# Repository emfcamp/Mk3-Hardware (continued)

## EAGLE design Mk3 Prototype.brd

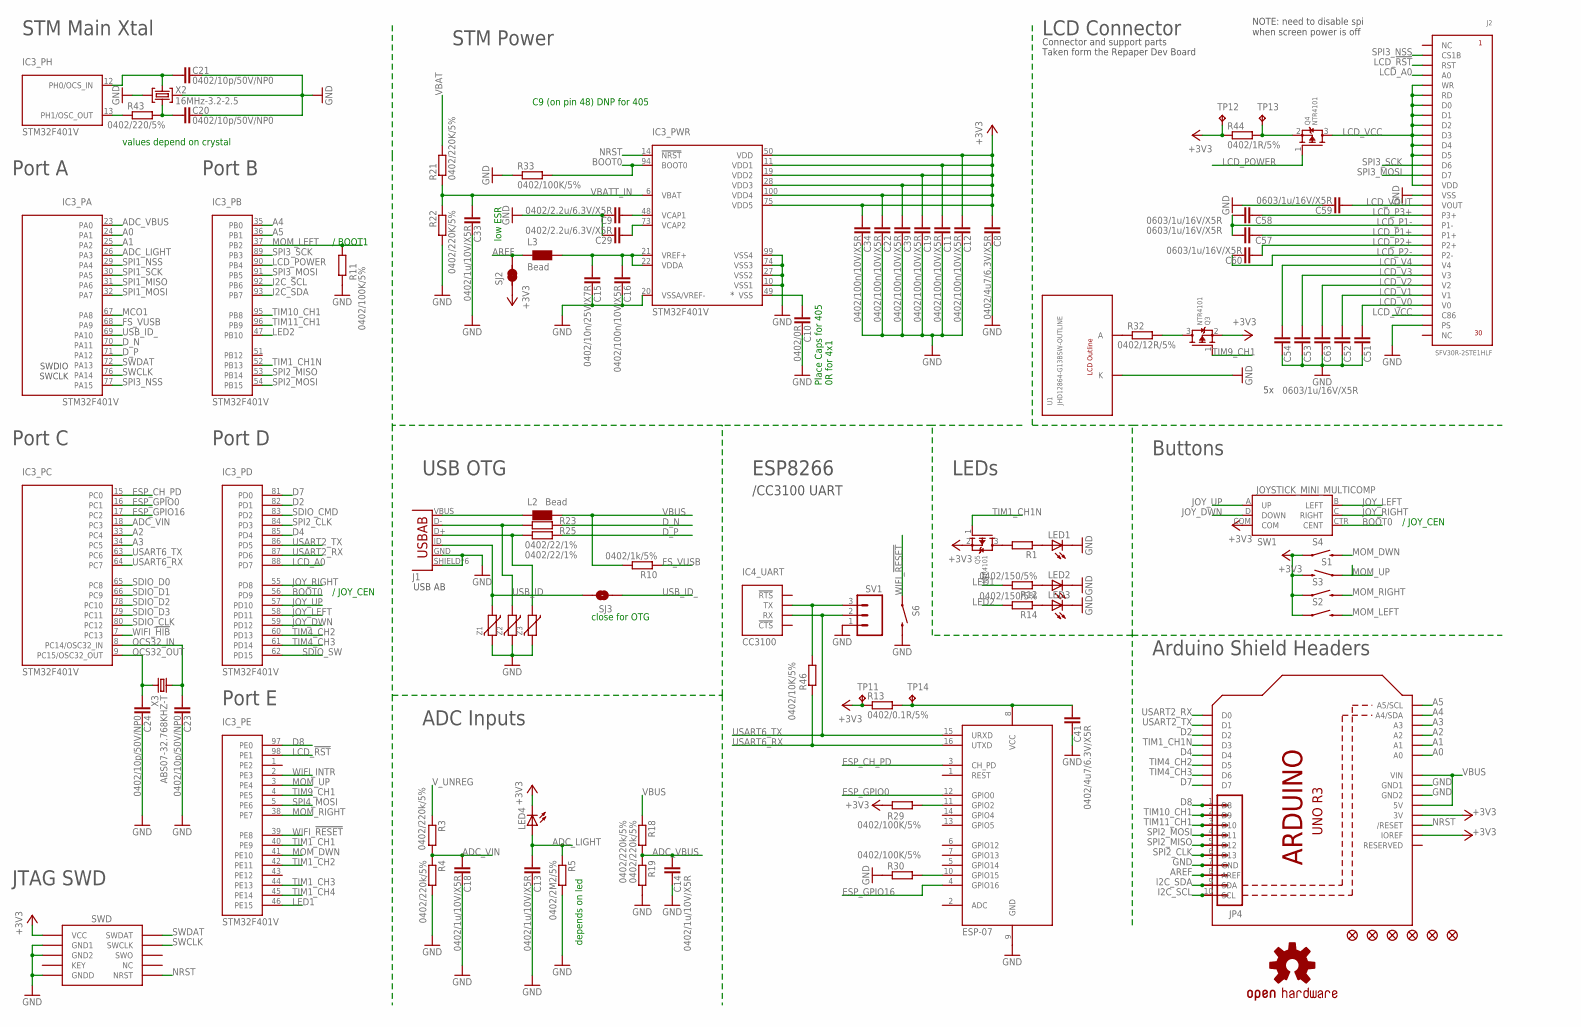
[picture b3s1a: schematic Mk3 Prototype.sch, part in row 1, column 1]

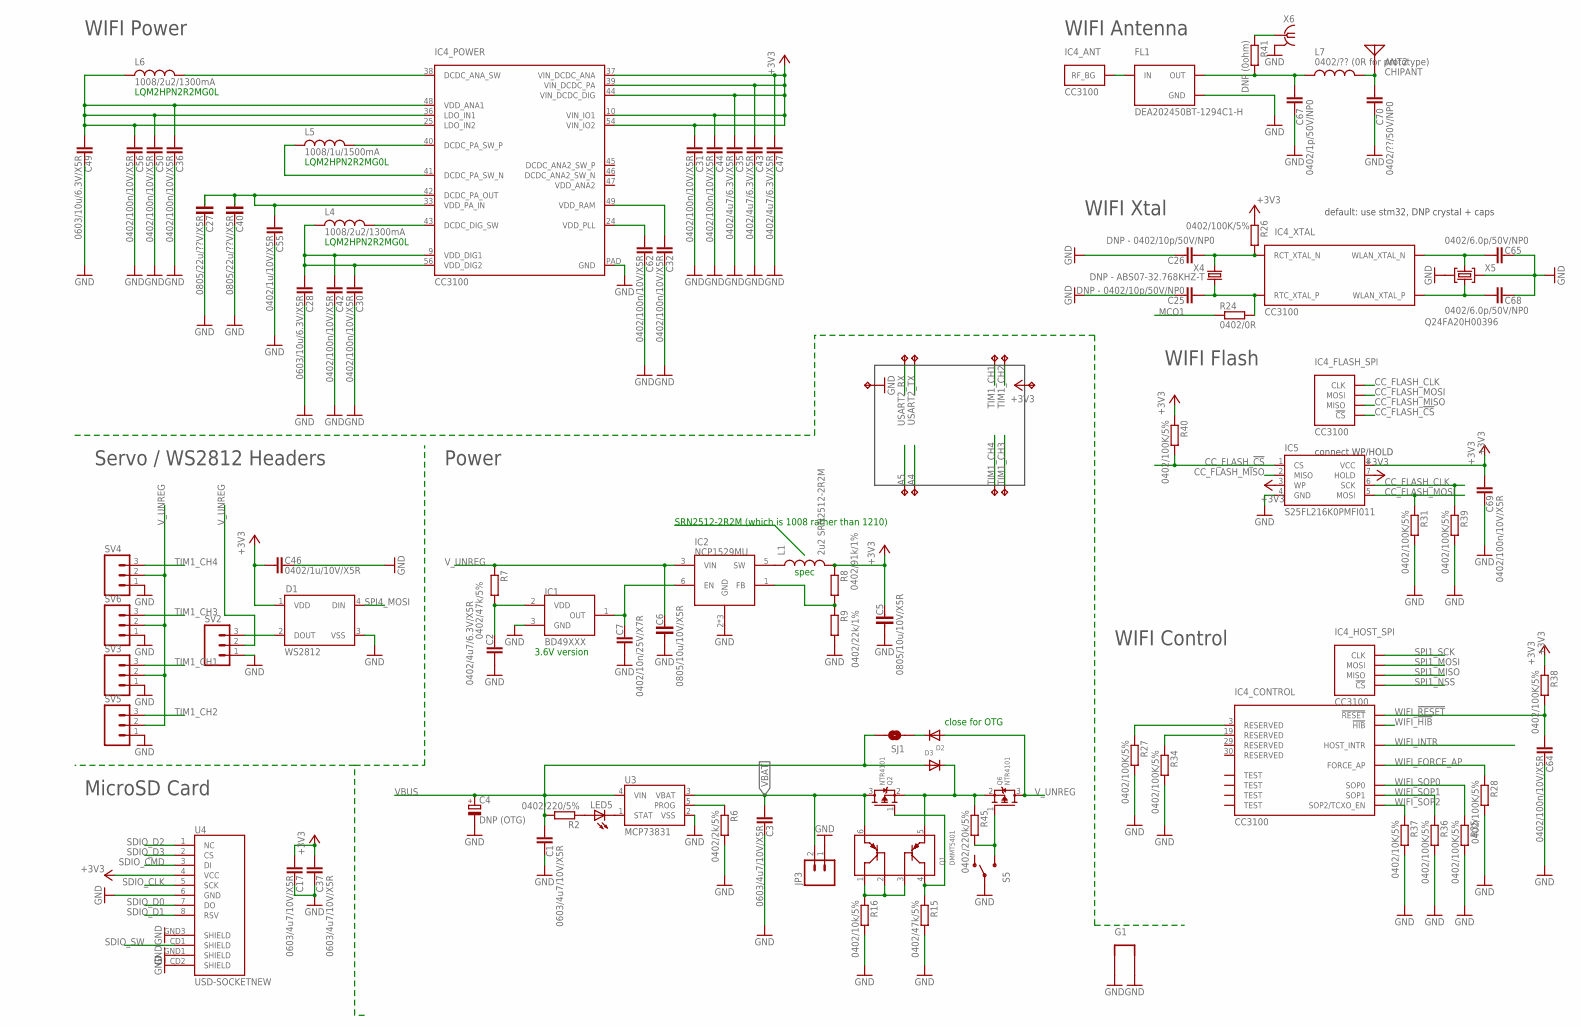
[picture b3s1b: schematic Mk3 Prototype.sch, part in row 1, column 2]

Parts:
ANT2: CHIPANT; 2450AT42A100
C1: 0603/4u7/10V/X5R; C0805K
C2, C8, C35, C41, C43, C47: 0402/4u7/6.3V/X5R; C0402-SMALLER
C3, C17, C37: 0603/4u7/10V/X5R; C0603K-SMALL
C4: DNP (OTG); E2,5-6
C5, C6: 0805/10u/10V/X5R; C0805-N
C7, C15: 0402/10n/25V/X7R; C0402-SMALLER
C9, C29: 0402/2.2u/6.3V/X5R; C0402-SMALLER
C10: 0402/0R; C0402-SMALLER
C11, C12, C16, C19, C22, C30, C31, C32, C34, C36, C39, C42, C44, C50, C56, C62, C64, C69: 0402/100n/10V/X5R; C0402-SMALLER
C13, C14, C18, C33, C46, C55: 0402/1u/10V/X5R; C0402-SMALLER
C20, C21, C23, C24: 0402/10p/50V/NP0; C0402-SMALLER
C25, C26: DNP - 0402/10p/50V/NP0; C0402-SMALLER
C27, C40: 0805/22u/??V/X5R; C0805-N
C28, C49: 0603/10u/6.3V/X5R; C0603K-SMALL
C51, C52, C53, C54, C57, C58, C59, C60, C63: 0603/1u/16V/X5R; C0603K-SMALL
C65, C68: 0402/6.0p/50V/NP0; C0402-SMALLER
C67: 0402/1p/50V/NP0; C0402-SMALLER
C70: 0402/??/50V/NP0; C0402-SMALLER
D1: WS2812B
D2, D3: DIODESOD-323F; SOD-323F
FID1, FID2, FID3, FID4, FID5, FID6: FIDUCIAL1X2.5-STOP; FIDUCIAL-1X2.5-STOP
FL1: DEA202450BT-1294C1-H; DEA202450BT
G1: GND-LOOP
IC1: BD49XXX; SSOP5
IC2: NCP1529MU; DFN6
IC3: STM32F401V; TQFP100
IC4: CC3100; VQFN-64
IC5: S25FL216K0PMFI011; SO08-EIAJ
J1: ZX62-AB-5PA(11); USB-AB-MICRO-SMD_LWK
J2: SFV30R-2STE1HLF
J3: SWD_SHROUD; SWD_PTH_SHROUD
JP3: M02-JST-2MM-SMT; JST-2-SMD
JP4: M10NOSILK; 1X10-NOSILK
L1: 2u2 SRN2512-2R2M; 1210
L2, L3: Bead; WUERTH-0805
L4, L6: 1008/2u2/1300mA; 1008
L5: 1008/1u/1500mA; 1008
L7: 0402/?? (0R for prototype); L0402
LED1: LED5MM
LED2, LED3, LED4, LED5: LED0603-CORRECT; LED-0603-CORRECT
LOGO1: OSHW-LOGOM; OSHW-LOGO-M
Q1: DMMT5401; SOT26
Q2, Q3, Q4, Q5, Q6: NTR4101; SOT23-R
R1: R-EU_0207/10; 0207/10
R2, R43: 0402/220/5%; R0402-SMALLER
R3, R4, R18, R19, R45: 0402/220k/5%; R0402-SMALLER
R5: 0402/2M2/5%; R0402-SMALLER
R6: 0402/2k/5%; R0402-SMALLER
R7, R15: 0402/47k/5%; R0402-SMALLER
R8: 0402/91k/1%; R0402-SMALLER
R9: 0402/22k/1%; R0402-SMALLER
R10: 0402/1k/5%; R0402-SMALLER
R11, R26, R27, R28, R29, R30, R31, R33, R34, R35, R36, R38, R39, R40: 0402/100K/5%; R0402-SMALLER
R12, R14: 0402/150/5%; R0402-SMALLER
R13: 0402/0.1R/5%; R0402-SMALLER
R16: 0402/10k/5%; R0402-SMALLER
R21, R22: 0402/220K/5%; R0402-SMALLER
R23, R25: 0402/22/1%; R0402-SMALLER
R24: 0402/0R; R0402-SMALLER
R32: 0402/12R/5%; R0402-SMALLER
R37, R46: 0402/10K/5%; R0402-SMALLER
R41: DNP (0ohm); R0402-SMALLER
R44: 0402/1R/5%; R0402-SMALLER
S1, S2, S3, S4: SWITCH-MOMENTARY-2; TACTILE_SWITCH_TALL
S5: SWITCH-SPST-SMD-A
S6: SWITCH-MOMENTARY-2SMD-1101NE; TACTILE-SWITCH-1101NE
SJ1, SJ3: JUMPER-PAD-2-NOYES_SILK; PAD-JUMPER-2-NO_YES_SILK
SJ2: SOLDERJUMPERTRACE; SJ_2S-TRACE
SV1, SV2, SV3, SV4, SV5, SV6: M03PTH; 1X03
SW1: JOYSTICK_MINI_MULTICOMP; JOYSTICK_MULTICOMP
TP1, TP2, TP3, TP4, TP5, TP6, TP7, TP8, TP9, TP10: TP4MM; 4MMEDGE
TP11, TP12, TP13, TP14: TPB1,27; B1,27
U1: JHD12864-G13BSW-OUTLINE
U2: ARDUINOR3-NODIM
U3: MCP73831; SOT23-5
U4: USD-SOCKETNEW; MICRO-SD-SOCKET-PP
X1: ESP-07
X2: 16MHz-3.2-2.5; CRYSTAL-3.2-2.5
X3: ABS07-32.768KHZ-T; RESONATOR_EPSON_FC_145
X4: DNP - ABS07-32.768KHZ-T; RESONATOR_EPSON_FC_145
X5: Q24FA20H00396; CRYSTAL-2.5X2.0
X6: MC-921
Z1, Z2, Z3: VARISTORCN0603; CT/CN0603

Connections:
+3V3: C5.1, C8.2, C11.2, C12.2, C17.2, C19.2, C22.2, C31.2, C34.2, C35.2, C37.2, C39.2, C43.2, C44.2, C46.2, C47.2, C69.2, D1.1 (VDD), IC3.11 (VDD1), IC3.19 (VDD2), IC3.28 (VDD3), IC3.50 (VDD), IC3.75 (VDD5), IC3.100 (VDD4), IC4.10 (VIN_IO1), IC4.37 (VIN_DCDC_ANA), IC4.39 (VIN_DCDC_PA), IC4.44 (VIN_DCDC_DIG), IC4.54 (VIN_IO2), IC5.3 (WP), IC5.7 (HOLD), IC5.8 (VCC), J3.1 (VCC), L1.2, LED4.C, Q3.2 (S), Q5.2 (S), R8.1, R13.1, R26.1, R29.1, R38.1, R40.1, R44.1, S1.B2 (2), S2.A2 (1), S3.A2 (1), S4.A2 (1), SJ2.1, SW1.COM, TP6.P$1, TP11.TP, TP12.TP, U2.3V, U2.IOREF, U4.4 (VCC)
A0: IC3.24 (PA1), U2.A0
A1: IC3.25 (PA2), U2.A1
A2: IC3.33 (PC4), U2.A2
A3: IC3.34 (PC5), U2.A3
A4: IC3.35 (PB0), TP8.P$1, U2.A4 (A4/SDA)
A5: IC3.36 (PB1), TP7.P$1, U2.A5 (A5/SCL)
ADC_LIGHT: C13.2, IC3.26 (PA3), LED4.A, R5.1
ADC_VBUS: C14.2, IC3.23 (PA0), R18.2, R19.1
ADC_VIN: C18.2, IC3.18 (PC3), R3.2, R4.1
ANT: ANT2.P$1, C70.1, L7.2
AREF: JP4.8, L3.1, SJ2.2, U2.AREF
BOOT0: IC3.56 (PD9), IC3.94 (BOOT0), R33.2, SW1.CTR (CENT)
CC_FLASH_!CS: IC4.14 (!CS), IC5.1 (CS), R40.2
CC_FLASH_CLK: IC4.11 (CLK), IC5.6 (SCK), R39.1
CC_FLASH_MISO: IC4.13 (MISO), IC5.2 (MISO)
CC_FLASH_MOSI: IC4.12 (MOSI), IC5.5 (MOSI), R31.1
CHARGING: LED5.C, U3.1 (STAT)
D2: IC3.82 (PD1), U2.D2
D4: IC3.85 (PD4), U2.D4
D7: IC3.81 (PD0), U2.D7
D8: IC3.97 (PE0), JP4.1, U2.D8
DFGFDG: C15.2, C16.2, IC3.21 (VREF+), IC3.22 (VDDA), L3.2
D_N: IC3.70 (PA11), R23.1
D_P: IC3.71 (PA12), R25.1
ESP_CH_PD: IC3.15 (PC0), X1.3 (CH_PD)
ESP_GPIO0: IC3.16 (PC1), X1.12 (GPIO0)
ESP_GPIO16: IC3.17 (PC2), X1.4 (GPIO16)
FS_VUSB: IC3.68 (PA9), R10.1
GND: C1.1, C2.2, C3.1, C4.-, C5.2, C6.2, C7.2, C8.1, C9.1, C10.1, C11.1, C12.1, C13.1, C14.1, C15.1, C16.1, C17.1, C18.1, C19.1, C20.1, C21.1, C22.1, C23.1, C24.1, C25.1, C26.1, C27.1, C28.1, C29.1, C30.1, C31.1, C32.1, C33.1, C34.1, C35.1, C36.1, C37.1, C39.1, C40.1, C41.1, C42.1, C43.1, C44.1, C46.1, C47.1, C49.1, C50.1, C51.1, C52.1, C53.1, C54.1, C55.1, C56.1, C59.1, C62.1, C63.1, C64.1, C65.1, C67.2, C68.1, C69.1, C70.2, D1.3 (VSS), FL1.GND@2 (GND), FL1.GND@4 (GND), G1.P$3 (1), G1.P$4 (2), IC1.3 (GND), IC2.2 (GND), IC2.4 (GND), IC2.EP (GND), IC3.10 (VSS1), IC3.20 (VSSA/VREF-), IC3.27 (VSS2), IC3.74 (VSS3), IC3.99 (VSS4), IC4.PAD (GND), IC5.4 (GND), J1.GND, J1.SHIELD, J1.SHIELD@0 (SHIELD), J1.SHIELD@1 (SHIELD), J1.SHIELD@2 (SHIELD), J1.SHIELD@3 (SHIELD), J1.SHIELD@5 (SHIELD), J2.16 (VSS), J2.29 (PS), J2.M1 (VSS), J2.M2 (VSS), J3.3 (GND1), J3.5 (GND2), J3.9 (GNDD), JP3.1, JP4.7, LED1.K (C), LED2.C, LED3.C, R4.2, R5.2, R6.2, R9.2, R11.1, R15.2, R16.2, R19.2, R22.2, R27.2, R28.2, R30.1, R31.2, R33.1, R34.2, R35.2, R36.2, R37.2, R39.2, S5.2, S6.2, SV1.1, SV2.1, SV3.1, SV4.1, SV5.1, SV6.1, TP5.P$1, U1.K, U2.GND, U2.GND1, U2.GND2, U3.2 (VSS), U4.6 (GND), U4.CD2 (SHIELD), U4.GND1 (SHIELD), U4.GND3 (SHIELD), X1.9 (GND), X2.2 (GND), X2.4 (GND)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
I2C_SCL: IC3.92 (PB6), JP4.10, U2.SCL
I2C_SDA: IC3.93 (PB7), JP4.9, U2.SDA
JOY_DWN: IC3.59 (PD12), SW1.D (DOWN)
JOY_LEFT: IC3.58 (PD11), SW1.B (LEFT)
JOY_RIGHT: IC3.55 (PD8), SW1.C (RIGHT)
JOY_UP: IC3.57 (PD10), SW1.A (UP)
LCD_!RST: IC3.98 (PE1), J2.3 (RST)
LCD_A0: IC3.88 (PD7), J2.4 (A0)
LCD_P1+: C57.2, J2.20 (P1+)
LCD_P1-: C57.1, C58.1, J2.19 (P1-)
LCD_P2+: C60.2, J2.21 (P2+)
LCD_P2-: C60.1, J2.22 (P2-)
LCD_P3+: C58.2, J2.18 (P3+)
LCD_POWER: IC3.90 (PB4), Q4.1 (G)
LCD_V0: C51.2, J2.27 (V0)
LCD_V1: C52.2, J2.26 (V1)
LCD_V2: C63.2, J2.25 (V2)
LCD_V3: C53.2, J2.24 (V3)
LCD_V4: C54.2, J2.23 (V4)
LCD_VCC: J2.5 (WR), J2.6 (RD), J2.7 (D0), J2.8 (D1), J2.9 (D2), J2.10 (D3), J2.11 (D4), J2.12 (D5), J2.15 (VDD), J2.28 (C86), Q4.3 (D)
LCD_VOUT: C59.2, J2.17 (VOUT)
LED1: IC3.46 (PE15), R12.2
LED2: IC3.47 (PB10), R14.2
MCO1: IC3.67 (PA8), R24.1
MOM_DWN: IC3.41 (PE10), S4.B2 (2)
MOM_LEFT: IC3.37 (PB2), R11.2, S2.B2 (2)
MOM_RIGHT: IC3.38 (PE7), S3.B2 (2)
MOM_UP: IC3.3 (PE4), S1.A2 (1)
unnamed: R32.1, U1.A
unnamed: C67.1, FL1.OUT, L7.1, R41.2
unnamed: FL1.IN, IC4.31 (RF_BG)
unnamed: C9.2, IC3.48 (VCAP1)
unnamed: C26.2, IC4.52 (RCT_XTAL_N), R26.2, X4.P$1 (1)
unnamed: Q1.4 (C2), Q2.1 (G), R15.1
unnamed: Q1.1 (C1), Q1.2 (B1), Q1.3 (B2), R16.1
unnamed: C65.2, IC4.22 (WLAN_XTAL_N), X5.3 (C2)
unnamed: C68.2, IC4.23 (WLAN_XTAL_P), X5.1 (C1)
unnamed: IC4.3 (RESERVED), R27.1
unnamed: IC4.19 (RESERVED), R34.1
unnamed: C7.1, IC1.1 (OUT), IC2.6 (EN)
unnamed: IC2.1 (FB), R8.2, R9.1
unnamed: D3.C, Q1.5 (E2), Q2.2 (S), Q6.2 (S), R45.1
unnamed: IC4.38 (DCDC_ANA_SW), L6.2
unnamed: C27.2, C40.2, C55.2, IC4.33 (VDD_PA_IN), IC4.42 (DCDC_PA_OUT)
unnamed: C36.2, C49.2, C50.2, C56.2, IC4.25 (LDO_IN2), IC4.36 (LDO_IN1), IC4.48 (VDD_ANA1), L6.1
unnamed: IC4.43 (DCDC_DIG_SW), L4.2
unnamed: C62.2, IC4.24 (VDD_PLL)
unnamed: D1.2 (DOUT), SV2.3
unnamed: C28.2, C30.2, C42.2, IC4.9 (VDD_DIG1), IC4.56 (VDD_DIG2), L4.1
unnamed: IC4.40 (DCDC_PA_SW_P), L5.2
unnamed: IC4.41 (DCDC_PA_SW_N), L5.1
unnamed: C32.2, IC4.49 (VDD_RAM)
unnamed: IC2.5 (SW), L1.1
unnamed: J1.VBUS, L2.1
unnamed: D2.C, SJ1.1
unnamed: C21.2, IC3.12 (PH0/OCS_IN), X2.3 (C2)
unnamed: C25.2, IC4.51 (RTC_XTAL_P), R24.2, X4.P$2 (2)
unnamed: C20.2, R43.2, X2.1 (C1)
unnamed: R6.1, U3.5 (PROG)
unnamed: LED5.A, R2.1
unnamed: C10.2, IC3.49 (VSS)
unnamed: C29.2, IC3.73 (VCAP2)
unnamed: R29.2, X1.11 (GPIO2)
unnamed: IC4.55 (TX), R46.2, SV1.3
unnamed: IC3.13 (PH1/OSC_OUT), R43.1
unnamed: R30.2, X1.10 (GPIO15)
unnamed: R41.1, X6.1
unnamed: LED3.A, R14.1
unnamed: LED2.A, R12.1
unnamed: Q4.2 (S), R44.2, TP13.TP
unnamed: Q6.1 (G), R45.2, S5.3 (S)
unnamed: C2.1, IC1.2 (VDD), R7.2
unnamed: Q3.3 (D), R32.2
unnamed: LED1.A, R1.1
unnamed: Q5.3 (D), R1.2
NRST: IC3.14 (!NRST), J3.10 (NRST), U2.RESET (/RESET)
OCS32_IN: C23.2, IC3.8 (PC14/OSC32_IN), X3.P$1 (1)
OCS32_OUT: C24.2, IC3.9 (PC15/OSC32_OUT), X3.P$2 (2)
SDIO_CLK: IC3.80 (PC12), U4.5 (SCK)
SDIO_CMD: IC3.83 (PD2), U4.3 (DI)
SDIO_D0: IC3.65 (PC8), U4.7 (DO)
SDIO_D1: IC3.66 (PC9), U4.8 (RSV)
SDIO_D2: IC3.78 (PC10), U4.1 (NC)
SDIO_D3: IC3.79 (PC11), U4.2 (CS)
SDIO_SW: IC3.62 (PD15), U4.CD1 (SHIELD)
SPI1_MISO: IC3.31 (PA6), IC4.7 (MISO)
SPI1_MOSI: IC3.32 (PA7), IC4.6 (MOSI)
SPI1_NSS: IC3.29 (PA4), IC4.8 (!CS)
SPI1_SCK: IC3.30 (PA5), IC4.5 (CLK)
SPI2_CLK: IC3.84 (PD3), JP4.6, U2.D13
SPI2_MISO: IC3.53 (PB14), JP4.5, U2.D12
SPI2_MOSI: IC3.54 (PB15), JP4.4, U2.D11
SPI3_MOSI: IC3.91 (PB5), J2.14 (D7)
SPI3_NSS: IC3.77 (PA15), J2.2 (CS1B)
SPI3_SCK: IC3.89 (PB3), J2.13 (D6)
SPI4_MOSI: D1.4 (DIN), IC3.5 (PE6)
SWCLK: IC3.76 (PA14), J3.4 (SWCLK)
SWDAT: IC3.72 (PA13), J3.2 (SWDAT)
TIM1_CH1: IC3.40 (PE9), SV3.3, TP3.P$1
TIM1_CH1N: IC3.52 (PB13), Q5.1 (G), U2.D3
TIM1_CH2: IC3.42 (PE11), SV5.3, TP4.P$1
TIM1_CH3: IC3.44 (PE13), SV6.3, TP10.P$1
TIM1_CH4: IC3.45 (PE14), SV4.3, TP9.P$1
TIM4_CH2: IC3.60 (PD13), U2.D5
TIM4_CH3: IC3.61 (PD14), U2.D6
TIM9_CH1: IC3.4 (PE5), Q3.1 (G)
TIM10_CH1: IC3.95 (PB8), JP4.2, U2.D9
TIM11_CH1: IC3.96 (PB9), JP4.3, U2.D10
USART2_RX: IC3.87 (PD6), TP1.P$1, U2.D0
USART2_TX: IC3.86 (PD5), TP2.P$1, U2.D1
USART6_RX: IC3.64 (PC7), R46.1, X1.16 (UTXD)
USART6_TX: IC3.63 (PC6), IC4.57 (RX), SV1.2, X1.15 (URXD)
USB_D_N: J1.D-, R23.2, Z2.1
USB_D_P: J1.D+, R25.2, Z3.1
USB_ID: J1.ID (USBID), SJ3.2, Z1.1
USB_ID_: IC3.69 (PA10), SJ3.1
VBAT: C3.2, JP3.2, Q1.6 (E1), Q2.3 (D), R21.2, U3.3 (VBAT)
VBATT_IN: C33.2, IC3.6 (VBAT), R21.1, R22.1
VBUS: C1.2, C4.+, D3.A, L2.2, R2.2, R10.2, R18.1, SJ1.2, U2.5V, U2.VIN, U3.4 (VIN)
VCC: C41.2, R13.2, TP14.TP, X1.8 (VCC)
V_UNREG: C6.1, D2.A, IC2.3 (VIN), Q6.3 (D), R3.1, R7.1, SV2.2, SV3.2, SV4.2, SV5.2, SV6.2
WIFI_!HIB: IC3.7 (PC13), IC4.2 (!HIB)
WIFI_!RESET: C64.2, IC3.39 (PE8), IC4.32 (!RESET), R38.2, S6.1
WIFI_FORCE_AP: IC4.4 (FORCE_AP), R28.1
WIFI_INTR: IC3.2 (PE3), IC4.15 (HOST_INTR)
WIFI_SOP0: IC4.35 (SOP0), R35.1
WIFI_SOP1: IC4.34 (SOP1), R36.1
WIFI_SOP2: IC4.21 (SOP2/TCXO_EN), R37.1

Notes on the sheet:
Arduino Shield Headers
LCD Connector
Taken form the Repaper Dev Board
Connector and support parts
WIFI Antenna
WIFI Flash
WIFI Xtal
LQM2HPN2R2MG0L
WIFI Power
WIFI Control
values depend on crystal
default: use stm32, DNP crystal + caps
connect WP/HOLD
Place Caps for 405 0R for 4x1
STM Power
STM Main Xtal
JTAG SWD
Port A
Port B
Port C
Port D
C9 (on pin 48) DNP for 405
spec
close for OTG
/ JOY_CEN
3.6V version
depends on led
/ BOOT1
low ESR
NOTE: need to disable spi when screen power is off
MicroSD Card
WS2812
Servo / WS2812 Headers
Port E
USB OTG
Power
LEDs
ESP8266
/CC3100 UART
ADC Inputs

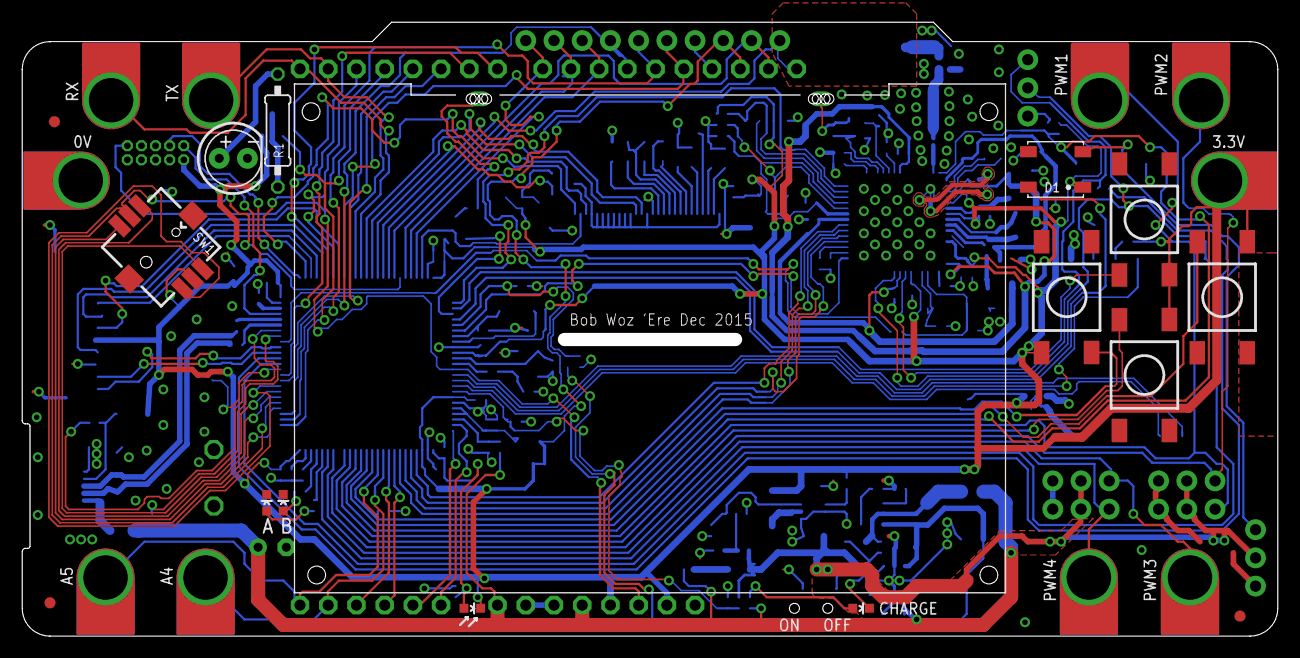
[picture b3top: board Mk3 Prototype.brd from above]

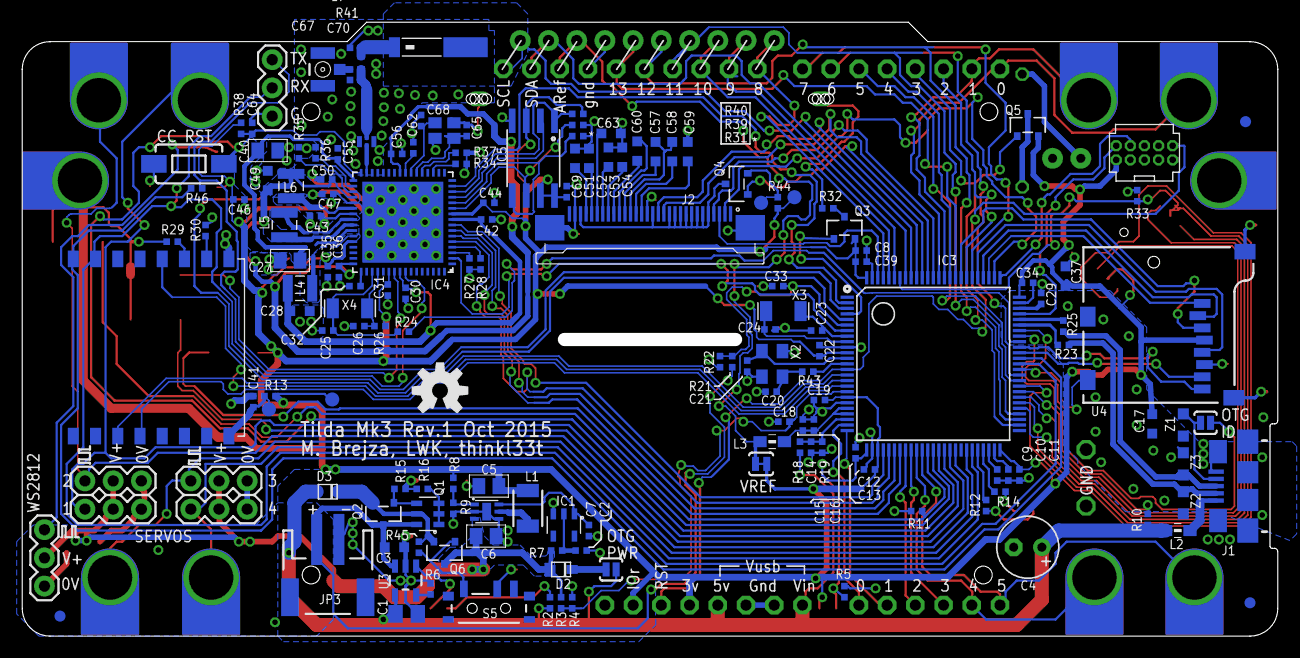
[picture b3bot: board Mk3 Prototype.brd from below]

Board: 2 copper layers, 113.0 x 55.2 mm, 192 parts (166 on the bottom side), 158 nets.

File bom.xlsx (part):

|  |  |  | Count
 |  | 0402/100n/10V/X5R |  | 18
 |  | 0402/1u/10V/X5R |  | 6
 |  | 0603/1u/16V/X5R |  | 9
 |  | 0402/4u7/6.3V/X5R |  | 6
 |  | 0603/4u7/10V/X5R |  | 4
 |  | 0402/2.2u/6.3V/X5R |  | 2
 |  | 0805/10u/10V/X5R |  | 2
 |  | 0603/10u/6.3V/X5R |  | 6
 |  | 0402/10n/25V/X7R |  | 2
Part |  | Value | Package
ANT1 |  | ANTENNA22500AT44M0400 | ANTENNA-CHIP_2500AT44M0400 | SparkFun- | RF | (77 54) | MR180
C1 |  | 0603/4u7/10V/X5R | C0805K | TiLDA Mk3 | Parts | (78.5 2) | MR180
C2 |  | 0402/4u7/6.3V/X5R | C0402-SMALLER | TiLDA Mk3 | Parts | (62.5 7.5) | MR0
C3 |  | 0603/4u7/10V/X5R | C0603K-SMALL | TiLDA Mk3 | Parts | (79.5 8) | MR180
C4 |  | DNP (OTG) | E2,5-6 | TiLDA Mk3 | Parts | (22.5 8) | MR180
C5 |  | 0805/10u/10V/X5R | C0805-N | passives- | 7351 | (75.5 9.5) | MR90
C6 |  | 0805/10u/10V/X5R | C0805-N | passives- | 7351 | (70 9.75) | MR90
C7 |  | 0402/10n/25V/X7R | C0402-SMALLER | TiLDA Mk3 | Parts | (66.75 12) | MR180
C8 |  | 0402/4u7/6.3V/X5R | C0402-SMALLER | TiLDA Mk3 | Parts | (41.9 14.3) | MR270
C9 |  | 0402/2.2u/6.3V/X5R | C0402-SMALLER | TiLDA Mk3 | Parts | (25.25 14.5) | MR90
C10 |  | 0402/0R | C0402-SMALLER | TiLDA Mk3 | Parts | (24.25 14.5) | MR90
C11 |  | 0402/100n/10V/X5R | C0402-SMALLER | TiLDA Mk3 | Parts | (23.25 14.5) | MR90
C12 |  | 0402/100n/10V/X5R | C0402-SMALLER | TiLDA Mk3 | Parts | (36.75 15) | MR0
C13 |  | 0402/1u/10V/X5R | C0402-SMALLER | TiLDA Mk3 | Parts | (38 16.5) | MR270
C14 |  | 0402/1u/10V/X5R | C0402-SMALLER | TiLDA Mk3 | Parts | (42 17) | MR90
C15 |  | 0402/10n/25V/X7R | C0402-SMALLER | TiLDA Mk3 | Parts | (42.75 19) | MR270
C16 |  | 0402/100n/10V/X5R | C0402-SMALLER | TiLDA Mk3 | Parts | (41.75 19) | MR270
C17 |  | 0603/4u7/10V/X5R | C0603K-SMALL | TiLDA Mk3 | Parts | (11.3 19.1) | MR90
C18 |  | 0402/1u/10V/X5R | C0402-SMALLER | TiLDA Mk3 | Parts | (44.45 19.3) | MR0
C19 |  | 0402/100n/10V/X5R | C0402-SMALLER | TiLDA Mk3 | Parts | (41.25 21.25) | MR0
C20 |  | 0402/6.2p/50V/NP0 | C0402-SMALLER | TiLDA Mk3 | Parts | (45.6 22) | MR0
C21 |  | 0402/6.2p/50V/NP0 | C0402-SMALLER | TiLDA Mk3 | Parts | (47.75 24.2) | MR90
C22 |  | 0402/100n/10V/X5R | C0402-SMALLER | TiLDA Mk3 | Parts | (42.048 25.686) | MR270
C23 |  | 0402/10p/50V/NP0 | C0402-SMALLER | TiLDA Mk3 | Parts | (42.5 27.5) | MR0
C24 |  | 0402/10p/50V/NP0 | C0402-SMALLER | TiLDA Mk3 | Parts | (46.2 27.6) | MR180
C25 |  | DNP - 0402/10p/50V/NP0 | C0402-SMALLER | TiLDA Mk3 | Parts | (85.5 28) | MR0
C26 |  | DNP - 0402/10p/50V/NP0 | C0402-SMALLER | TiLDA Mk3 | Parts | (83 28) | MR0
C27 |  | 0603/??u/6.3V/X5R | C0603K-SMALL | TiLDA Mk3 | Parts | (88 28.25) | MR180
C28 |  | 0603/10u/6.3V/X5R | C0603K-SMALL | TiLDA Mk3 | Parts | (88 29.75) | MR180
C29 |  | 0402/2.2u/6.3V/X5R | C0402-SMALLER | TiLDA Mk3 | Parts | (21.298 30.388) | MR270
C30 |  | 0402/100n/10V/X5R | C0402-SMALLER | TiLDA Mk3 | Parts | (78.5 30.85) | MR90
C31 |  | 0402/100n/10V/X5R | C0402-SMALLER | TiLDA Mk3 | Parts | (80.1 31.15) | MR90
C32 |  | 0402/100n/10V/X5R | C0402-SMALLER | TiLDA Mk3 | Parts | (83.05 31.5) | MR0
C33 |  | 0402/1u/10V/X5R | C0402-SMALLER | TiLDA Mk3 | Parts | (45 31.5) | MR0
C34 |  | 0402/100n/10V/X5R | C0402-SMALLER | TiLDA Mk3 | Parts | (22.516 31.798) | MR180
C35 |  | 0402/4u7/6.3V/X5R | C0402-SMALLER | TiLDA Mk3 | Parts | (85.5 32.8) | MR90
C36 |  | 0402/100n/10V/X5R | C0402-SMALLER | TiLDA Mk3 | Parts | (84.5 32.8) | MR90
C37 |  | 0603/4u7/10V/X5R | C0603K-SMALL | TiLDA Mk3 | Parts | (19.1 32.9) | MR270
C38 |  | 0603/10u/6.3V/X5R | C0603K-SMALL | TiLDA Mk3 | Parts | (89 34) | MR0
C39 |  | 0402/100n/10V/X5R | C0402-SMALLER | TiLDA Mk3 | Parts | (37.5 34) | MR180
C41 |  | 0402/4u7/6.3V/X5R | C0402-SMALLER | TiLDA Mk3 | Parts | (93.5 35.4) | MR0
C42 |  | 0402/100n/10V/X5R | C0402-SMALLER | TiLDA Mk3 | Parts | (71 37.5) | MR180
C43 |  | 0402/4u7/6.3V/X5R | C0402-SMALLER | TiLDA Mk3 | Parts | (86.6 37.8) | MR0
C44 |  | 0402/100n/10V/X5R | C0402-SMALLER | TiLDA Mk3 | Parts | (71 38.5) | MR180
C45 |  | 0603/10u/6.3V/X5R | C0603K-SMALL | TiLDA Mk3 | Parts | (93 39) | MR0
C46 |  | 0402/1u/10V/X5R | C0402-SMALLER | TiLDA Mk3 | Parts | (99 39.5) | MR0
C47 |  | 0402/4u7/6.3V/X5R | C0402-SMALLER | TiLDA Mk3 | Parts | (85.6 39.8) | MR0
C48 |  | 0603/10u/6.3V/X5R | C0603K-SMALL | TiLDA Mk3 | Parts | (93 40.5) | MR0
C49 |  | 0603/10u/6.3V/X5R | C0603K-SMALL | TiLDA Mk3 | Parts | (90.9 41) | MR270
C50 |  | 0402/100n/10V/X5R | C0402-SMALLER | TiLDA Mk3 | Parts | (85.6 41.1) | MR0
C51 |  | 0603/1u/16V/X5R | C0603K-SMALL | TiLDA Mk3 | Parts | (63.25 43) | MR270
C52 |  | 0603/1u/16V/X5R | C0603K-SMALL | TiLDA Mk3 | Parts | (62 43) | MR270
C53 |  | 0603/1u/16V/X5R | C0603K-SMALL | TiLDA Mk3 | Parts | (60.25 43.1) | MR270
C54 |  | 0603/1u/16V/X5R | C0603K-SMALL | TiLDA Mk3 | Parts | (59 43.1) | MR270
C55 |  | 0402/1u/10V/X5R | C0402-SMALLER | TiLDA Mk3 | Parts | (84.6 43.4) | MR270
C56 |  | 0402/100n/10V/X5R | C0402-SMALLER | TiLDA Mk3 | Parts | (79.3 43.4) | MR180
C57 |  | 0603/1u/16V/X5R | C0603K-SMALL | TiLDA Mk3 | Parts | (56 43.6) | MR270
C58 |  | 0603/1u/16V/X5R | C0603K-SMALL | TiLDA Mk3 | Parts | (54.5 43.6) | MR270
C59 |  | 0603/1u/16V/X5R | C0603K-SMALL | TiLDA Mk3 | Parts | (53.1 43.6) | MR270
C60 |  | 0603/1u/16V/X5R | C0603K-SMALL | TiLDA Mk3 | Parts | (57.65 43.65) | MR90
C61 |  | 0603/10u/6.3V/X5R | C0603K-SMALL | TiLDA Mk3 | Parts | (89.2 43.9) | MR90
C62 |  | 0402/100n/10V/X5R | C0402-SMALLER | TiLDA Mk3 | Parts | (77.8 43.95) | MR270
C63 |  | 0603/1u/16V/X5R | C0603K-SMALL | TiLDA Mk3 | Parts | (60 45.25) | MR180
C64 |  | 0402/100n/10V/X5R | C0402-SMALLER | TiLDA Mk3 | Parts | (92.5 45.5) | MR270
C65 |  | 0402/6p2/100V/NP0 | C0402-SMALLER | TiLDA Mk3 | Parts | (73 45.5) | MR270
C67 |  | 0402/1p/50V/NP0 | C0402-SMALLER | TiLDA Mk3 | Parts | (81.5 46.25) | MR0
C68 |  | 0402/6p2/100V/NP0 | C0402-SMALLER | TiLDA Mk3 | Parts | (77.1 46.4) | MR270
C69 |  | 0402/100n/10V/X5R | C0402-SMALLER | TiLDA Mk3 | Parts | (70 46.5) | MR270
C70 |  | 0402/??/50V/NP0 | C0402-SMALLER | TiLDA Mk3 | Parts | (72.5 50.25) | MR0
D1 |  |  | WS2812B | SparkFun- | LED | (93 42) | R180
D2 |  |  | SOD123 | TiLDA Mk3 | Parts | (64.5 6) | MR180
D3 |  |  | SOD123 | TiLDA Mk3 | Parts | (88.5 12.5) | MR270
FID1 |  | FIDUCIAL1X2.5-STOP | FIDUCIAL-1X2.5-STOP | TiLDA Mk3 | Parts | (3.5 46) | R90
FID2 |  | FIDUCIAL1X2.5-STOP | FIDUCIAL-1X2.5-STOP | TiLDA Mk3 | Parts | (101.2 7.5) | R0
FID3 |  | FIDUCIAL1X2.5-STOP | FIDUCIAL-1X2.5-STOP | TiLDA Mk3 | Parts | (2.5 6) | R0
FID4 |  | FIDUCIAL1X2.5-STOP | FIDUCIAL-1X2.5-STOP | TiLDA Mk3 | Parts | (2.5 6) | MR0
FID5 |  | FIDUCIAL1X2.5-STOP | FIDUCIAL-1X2.5-STOP | TiLDA Mk3 | Parts | (101.2 7.5) | MR0
FID6 |  | FIDUCIAL1X2.5-STOP | FIDUCIAL-1X2.5-STOP | TiLDA Mk3 | Parts | (3.5 46) | MR90
FL1 |  | DEA202450BT-1294C1-H | DEA202450BT | TiLDA Mk3 | Parts | (82 44.5) | MR0
G1 |  | GND-LOOP | GND-LOOP | dtb |  | (17.25 14.25) | MR270
IC1 |  | BD49XXX | SSOP5 | TiLDA Mk3 | Parts | (62.75 9.5) | MR180
IC2 |  | AP3419 | SOT26 | TiLDA Mk3 | Parts | (67.5 9.75) | MR180
IC3 |  | STM32F401V | TQFP100 | TiLDA Mk3 | Parts | (31 24.5) | MR270
IC4 |  | CC3100 | VQFN-64 | TiLDA Mk3 | Parts | (78.75 37.25) | MR90
IC5 |  | S25FL216K0PMFI011 | SO08-EIAJ | TiLDA Mk3 | Parts | (67 43) | MR180
J1 |  | ZX62-AB-5PA(11) | USB-AB-MICRO-SMD_LWK | TiLDA Mk3 | Parts | (2.7 13.5) | MR180
J2 |  | SFV30R-2STE1HLF | SFV30R-2STE1HLF | TiLDA Mk3 | Parts | (56.5 35.2) | MR180
J3 |  | SWD_SHROUD | SWD_PTH_SHROUD | dtb |  | (12 43.5) | MR0
JP1 |  | JOYSTICK_MINI_MULTICOMP | JOYSTICK_MULTICOMP | TiLDA Mk3 | Parts | (12.5 35) | R315
JP2 |  |  | PINHEAD_2X05_127 | TiLDA Mk3 | Parts | (78.5 -3) | R90
JP3 |  |  | JST-2-SMD | TiLDA Mk3 | Parts | (85.5 5) | MR180
JP4 |  | M10SILK_FEMALE_PTH | 1X10 | SparkFun- | Connectors | (45.3175 53.59875) | MR180
L1 |  |  | 1210 | TiLDA Mk3 | Parts | (72.5 9.5) | MR270
L2 |  | Bead | WUERTH-0805 | TiLDA Mk3 | Parts | (9 9.5) | MR180
L3 |  | Bead | WUERTH-0805 | TiLDA Mk3 | Parts | (45.5 17.5) | MR0
L4 |  | 1008/2u2/1300mA | 1008 | TiLDA Mk3 | Parts | (88 32) | MR0
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
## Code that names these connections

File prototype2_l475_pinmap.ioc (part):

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Mcu.Name=STM32L475V(C-E-G)Tx
Mcu.Package=LQFP100
Mcu.UserName=STM32L475VGTx
PA0.Signal=S_TIM2_CH1_ETR
PA1.Signal=S_TIM2_CH2
PA10.Mode=OTG/Dual_Role_Device
PA10.Signal=USB_OTG_FS_ID
PA11.Mode=OTG/Dual_Role_Device
PA11.Signal=USB_OTG_FS_DM
PA12.Mode=OTG/Dual_Role_Device
PA12.Signal=USB_OTG_FS_DP
PA13.Mode=Serial-Wire
PA13.Signal=SYS_JTMS-SWDIO
PA14.Mode=Serial-Wire
PA14.Signal=SYS_JTCK-SWCLK
PA15.GPIOParameters=GPIO_Label
PA15.GPIO_Label=button
PA15.Signal=GPIO_Input
PA2.Signal=S_TIM2_CH3
PA3.Signal=S_TIM2_CH4
PA4.Mode=NSS_Signal_Hard
PA4.Signal=SPI1_NSS
PA5.Signal=COMP_DAC12_group
PA6.Mode=Full_Duplex_Master
PA6.Signal=SPI1_MISO
PA7.Mode=Full_Duplex_Master
PA7.Signal=SPI1_MOSI
PA8.GPIOParameters=GPIO_Label
PA8.GPIO_Label=SDIO_SW
PA8.Signal=GPIO_Input
PA9.Mode=Activate_VBUS
PA9.Signal=USB_OTG_FS_VBUS
PB0.Signal=ADCx_IN15
PB1.GPIOParameters=GPIO_Label
PB1.GPIO_Label=ADC_LIGHT
PB1.Signal=ADCx_IN16
PB10.Mode=Full_Duplex_Master
PB10.Signal=SPI2_SCK
PB12.Mode=NSS_Signal_Hard
PB12.Signal=SPI2_NSS
PB13.Mode=Output Compare1 CH1N
PB13.Signal=TIM15_CH1N
PB14.Mode=Full_Duplex_Master
PB14.Signal=SPI2_MISO
PB15.Mode=Full_Duplex_Master
PB15.Signal=SPI2_MOSI
PB3.Mode=Full_Duplex_Master
PB3.Signal=SPI3_SCK
PB4.Mode=Full_Duplex_Master
PB4.Signal=SPI3_MISO
PB5.Mode=Full_Duplex_Master
PB5.Signal=SPI3_MOSI
PB6.Mode=Asynchronous
PB6.Signal=USART1_TX
PB7.Mode=Asynchronous
PB7.Signal=USART1_RX
PB8.Mode=I2C
PB8.Signal=I2C1_SCL
PB9.Mode=I2C
PB9.Signal=I2C1_SDA
PC0.Mode=I2C
PC0.Signal=I2C3_SCL
PC1.Mode=I2C
PC1.Signal=I2C3_SDA
PC10.Mode=SD_4_bits_Wide_bus
PC10.Signal=SDMMC1_D2
PC11.Mode=SD_4_bits_Wide_bus
PC11.Signal=SDMMC1_D3
PC12.Mode=SD_4_bits_Wide_bus
PC12.Signal=SDMMC1_CK
PC13.GPIOParameters=GPIO_Label
PC13.GPIO_Label=IMU_IRQ2
PC13.Signal=GPIO_Input
PC14/OSC32_IN.Mode=LSE-External-Oscillator
PC14/OSC32_IN.Signal=RCC_OSC32_IN
PC15/OSC32_OUT.Mode=LSE-External-Oscillator
PC15/OSC32_OUT.Signal=RCC_OSC32_OUT
PC3.GPIOParameters=GPIO_Label
PC3.GPIO_Label=ADC_VIN
PC3.Signal=ADCx_IN4
PC4.Mode=Asynchronous
PC4.Signal=USART3_TX
PC5.Mode=Asynchronous
PC5.Signal=USART3_RX
PC6.GPIOParameters=GPIO_Label
PC6.GPIO_Label=cc_hib
PC6.Signal=GPIO_Output
PC7.GPIOParameters=GPIO_Label
PC7.GPIO_Label=TIM8_CH2 (LED)
PC7.Signal=S_TIM8_CH2
PC8.Mode=SD_4_bits_Wide_bus
PC8.Signal=SDMMC1_D0
PC9.Mode=SD_4_bits_Wide_bus
PC9.Signal=SDMMC1_D1
PD0.Mode=8b-d1
PD0.Signal=FMC_D2
PD1.Mode=8b-d1
PD1.Signal=FMC_D3
PD10.Signal=GPIO_Input
PD11.Signal=GPIO_Input
PD12.GPIOParameters=GPIO_Label
PD12.GPIO_Label=buzz tim4_ch1
PD12.Signal=S_TIM4_CH1
PD13.Signal=GPIO_Output
PD14.Mode=8b-d1
PD14.Signal=FMC_D0
PD15.Mode=8b-d1
PD15.Signal=FMC_D1
PD2.Mode=SD_4_bits_Wide_bus
PD2.Signal=SDMMC1_CMD
PD3.Signal=GPIO_Input
PD4.Mode=Lcd1
PD4.Signal=FMC_NOE
PD5.Mode=Lcd1
PD5.Signal=FMC_NWE
PD6.Signal=GPIO_Input
PD7.Mode=NorPsramChipSelect1_1
PD7.Signal=FMC_NE1
PD8.Signal=GPIO_Input
PD9.Signal=GPIO_Input
PE0.Signal=GPIO_Input
PE1.GPIOParameters=GPIO_Label
PE1.GPIO_Label=BL TIM17_CH1
PE1.Signal=S_TIM17_CH1
PE10.Mode=8b-d1
PE10.Signal=FMC_D7
PE11.Signal=S_TIM1_CH2
PE12.GPIOParameters=GPIO_Label
PE12.GPIO_Label=LED
PE12.Signal=GPIO_Output
PE13.Mode=Full_Duplex_Master
PE13.Signal=SPI1_SCK
PE14.Signal=S_TIM1_CH4
PE15.GPIOParameters=GPIO_Label
PE15.GPIO_Label=LED
PE15.Signal=GPIO_Output
PE2.Mode=A23_1
PE2.Signal=FMC_A23
PE3.GPIOParameters=GPIO_Label
PE3.GPIO_Label=CC_RST
PE3.Signal=GPIO_Output
PE4.GPIOParameters=GPIO_Label
PE4.GPIO_Label=CC_IRQ
PE4.Signal=GPIO_Output
PE5.GPIOParameters=GPIO_Label
PE5.GPIO_Label=TEAR
PE5.Signal=GPIO_Input
PE6.GPIOParameters=GPIO_Label
PE6.GPIO_Label=LCD_MODE
PE6.Signal=GPIO_Output
PE7.Mode=8b-d1
PE7.Signal=FMC_D4
PE8.Mode=8b-d1
PE8.Signal=FMC_D5
PE9.Mode=8b-d1
PE9.Signal=FMC_D6
RCC.HSE_VALUE=8000000

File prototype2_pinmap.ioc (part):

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Mcu.Name=STM32F407V(E-G)Tx
Mcu.Package=LQFP100
Mcu.UserName=STM32F407VETx
PA0-WKUP.Signal=S_TIM2_CH1_ETR
PA1.Signal=S_TIM2_CH2
PA10.Mode=OTG/Dual_Role_Device
PA10.Signal=USB_OTG_FS_ID
PA11.Mode=OTG/Dual_Role_Device
PA11.Signal=USB_OTG_FS_DM
PA12.Mode=OTG/Dual_Role_Device
PA12.Signal=USB_OTG_FS_DP
PA13.Mode=Serial-Wire
PA13.Signal=SYS_JTMS-SWDIO
PA14.Mode=Serial-Wire
PA14.Signal=SYS_JTCK-SWCLK
PA2.Signal=S_TIM2_CH3
PA3.Signal=S_TIM2_CH4
PA4.Mode=NSS_Signal_Hard
PA4.Signal=SPI1_NSS
PA5.Mode=Full_Duplex_Master
PA5.Signal=SPI1_SCK
PA6.GPIOParameters=GPIO_Label
PA6.GPIO_Label=CC_MISO
PA6.Mode=Full_Duplex_Master
PA6.Signal=SPI1_MISO
PA7.Mode=Full_Duplex_Master
PA7.Signal=SPI1_MOSI
PA9.Mode=Activate_VBUS
PA9.Signal=USB_OTG_FS_VBUS
PB10.Mode=I2C
PB10.Signal=I2C2_SCL
PB11.Mode=I2C
PB11.Signal=I2C2_SDA
PB12.Mode=NSS_Signal_Hard
PB12.Signal=SPI2_NSS
PB13.Mode=Full_Duplex_Master
PB13.Signal=SPI2_SCK
PB14.Mode=Full_Duplex_Master
PB14.Signal=SPI2_MISO
PB15.Mode=Full_Duplex_Master
PB15.Signal=SPI2_MOSI
PB3.GPIOParameters=GPIO_Label
PB3.GPIO_Label=spi3_clk_lcd
PB3.Mode=Full_Duplex_Master
PB3.Signal=SPI3_SCK
PB4.GPIOParameters=GPIO_Label
PB4.GPIO_Label=spi3_miso_lcd
PB4.Mode=Full_Duplex_Master
PB4.Signal=SPI3_MISO
PB5.GPIOParameters=GPIO_Label
PB5.GPIO_Label=spi3_mosi_lcd
PB5.Mode=Full_Duplex_Master
PB5.Signal=SPI3_MOSI
PB6.GPIOParameters=GPIO_Label
PB6.GPIO_Label=CC3100_TX
PB6.Mode=Asynchronous
PB6.Signal=USART1_TX
PB7.GPIOParameters=GPIO_Label
PB7.GPIO_Label=CC3100_RX
PB7.Mode=Asynchronous
PB7.Signal=USART1_RX
PB8.Mode=I2C
PB8.Signal=I2C1_SCL
PB9.Mode=I2C
PB9.Signal=I2C1_SDA
PC10.Mode=SD_4_bits_Wide_bus
PC10.Signal=SDIO_D2
PC11.Mode=SD_4_bits_Wide_bus
PC11.Signal=SDIO_D3
PC12.Mode=SD_4_bits_Wide_bus
PC12.Signal=SDIO_CK
PC14-OSC32_IN.Mode=LSE-External-Oscillator
PC14-OSC32_IN.Signal=RCC_OSC32_IN
PC15-OSC32_OUT.Mode=LSE-External-Oscillator
PC15-OSC32_OUT.Signal=RCC_OSC32_OUT
PC6.Mode=Asynchronous
PC6.Signal=USART6_TX
PC7.Mode=Asynchronous
PC7.Signal=USART6_RX
PC8.Mode=SD_4_bits_Wide_bus
PC8.Signal=SDIO_D0
PC9.Mode=SD_4_bits_Wide_bus
PC9.Signal=SDIO_D1
PD0.Mode=8b-d1
PD0.Signal=FSMC_D2
PD1.Mode=8b-d1
PD1.Signal=FSMC_D3
PD13.GPIOParameters=GPIO_Label
PD13.GPIO_Label=tim4_ch2_lcdback
PD13.Signal=S_TIM4_CH2
PD14.Mode=8b-d1
PD14.Signal=FSMC_D0
PD15.Mode=8b-d1
PD15.Signal=FSMC_D1
PD2.Mode=SD_4_bits_Wide_bus
PD2.Signal=SDIO_CMD
PD4.Mode=Lcd1
PD4.Signal=FSMC_NOE
PD5.Mode=Lcd1
PD5.Signal=FSMC_NWE
PD7.Mode=NorPsramChipSelect1_1
PD7.Signal=FSMC_NE1
PE10.Mode=8b-d1
PE10.Signal=FSMC_D7
PE11.Signal=S_TIM1_CH2
PE13.Signal=S_TIM1_CH3
PE14.Signal=S_TIM1_CH4
PE2.Mode=A23_1
PE2.Signal=FSMC_A23
PE5.Signal=S_TIM9_CH1
PE7.Mode=8b-d1
PE7.Signal=FSMC_D4
PE8.Mode=8b-d1
PE8.Signal=FSMC_D5
PE9.Mode=8b-d1
PE9.Signal=FSMC_D6
PH0-OSC_IN.Mode=HSE-External-Oscillator
PH0-OSC_IN.Signal=RCC_OSC_IN
PH1-OSC_OUT.Mode=HSE-External-Oscillator
PH1-OSC_OUT.Signal=RCC_OSC_OUT
RCC.HSE_VALUE=25000000
RCC.SYSCLKFreq_VALUE=16000000

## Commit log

2015-08-28 submoduling libraries
2015-08-29 Adding parts library file base off MKe Adding DRU and CAM job Add licence to Readme
2015-08-29 Adding STM42F401R Part
2015-08-29 Adding CC3100 part
2015-08-29 Throwing initial parts on board for prototype
2015-08-29 Remove unused submodules
2015-08-29 Adding some parts datasheets
2015-08-29 Adding WIFI antenna and filter parts
2015-08-29 Adding 2.5x2.0 xtal footprint
2015-08-29 Adding 1008 footprint and some datasheets
2015-08-29 CC3100 Basic power hook up done
2015-08-29 done stm32 power, HSE, SWD, SD card, some usb
2015-08-29 finished stm32 power, done sd power
2015-08-29 adding large edge connectors
2015-08-30 initial place and route of wifi section
2015-08-30 started to wire the stm32, very rough route to get idea of spacing stuff out
2015-08-30 moving a few parts around
2015-08-30 added some comments, moved a couple of things around
2015-08-31 Lots of schematic clean up
2015-08-31 making board symmetrical
2015-08-31 added gnd loop
2015-08-31 adding stm32f401v
2015-08-31 starting stm32 100pin schematic
2015-08-31 arduino gpio wired
2015-08-31 added servos and neopixel
2015-08-31 wired servos and a few control signals
2015-09-01 added esp07
2015-09-01 adding esp, bit more wiring
2015-09-01 wired a few more things
2015-09-01 a few notes added
2015-09-01 making note clearer
2015-09-06 all peripherals assigned to stm32
2015-09-06 started stm32 fanout
2015-09-06 stm32 fanouted
2015-09-06 few notes added, some minor routing
2015-09-06 bit more routing
2015-09-07 power section worked on
2015-09-07 made gpio headers stripbord happy
2015-09-08 musical spi ports complete
2015-09-08 rf bit changed
2015-09-08 a little more decoupling
2015-09-08 improved placement of flash IC
2015-09-08 some more power routing for the cc
2015-09-09 added low voltage cutoff
2015-09-09 moving pins so the lcd has its hardware CS
2015-09-09 added notes, increased via size
2015-09-10 added two status leds
2015-09-11 power supply improvments
2015-09-12 bit of tidying up
2015-09-12 some routing tidying
2015-09-12 redone some of the cc spi routing
2015-09-12 moved routing a little
2015-09-13 improving routing around usb
2015-09-13 added part no for mosfets
2015-09-13 bit of wiring and routing
2015-09-13 part numbers added, routing tidied
2015-09-14 rotating switches so route better
2015-09-15 5mm led added
2015-09-16 added usb esd protection, some routing
2015-09-26 placed usb esd
2015-09-26 making usb socket flush
2015-09-26 getting through the bom
2015-09-26 some routing
2015-09-26 more routing
2015-09-27 chnaged regulator to ncp..., all routed (for now)
2015-09-28 added series resistor to stm32 crystal
2015-09-28 added comment about switch
2015-10-21 changing 4x0603->2x0805, power mosfet, lcd mosfet
2015-10-21 wiring cc programming interface to stm32
2015-10-29 lots of cleaing up, silk screen, drc fixes
2015-10-29 more little bits and pieces; current shunt on esp
2015-10-29 moving parts around a little
2015-10-29 minor routing updates, cam now has tNames, bNames
2015-10-29 first prototype pretty much done
2015-10-31 minor touchups
2015-11-01 schematic tidyied up
2015-11-01 more tidying
2015-11-02 adding pdf and bom
2015-11-02 minor change
2015-11-02 adding some more files
2015-12-15 Removed errant R42 resisitor and old antenna footprint
2015-12-15 Added gerbers as ordered Dec 15th 2015
2015-12-29 tweeking values of crystal caps
2015-12-29 updating some part values
2015-12-29 one part value changed
2016-02-01 added note on R45, added value to stm32 crystal
2016-02-01 updated stm32 crystal cap vales
2016-02-01 updating some part values from the spreadsheet bom
2016-03-18 adding a part
2016-03-24 started v2
2016-03-27 more work on v2
2016-03-28 initial schematic of v2 done
2016-03-28 more schematic stuff
2016-03-29 moving parts around a bit
2016-03-30 changing to 2.4 screen, 0603 componments
2016-04-02 some more routing
2016-04-02 moved bits around, changed outline
2016-04-03 started adding battery protection uc
2016-04-04 aligning some parts better
2016-04-04 starting cc3100 breakout
2016-04-08 started to rework pin mapping a little so the lcd uses the FSMC pins
2016-04-08 some poking
2016-04-10 more part specing
2016-04-11 changing mosfet part
2016-04-11 changed battery charger IC
2016-04-15 making compatible with l4
2016-04-16 added some notes
2016-04-16 schamtic done
2016-04-16 load more routing
2016-04-17 getting there...
2016-04-17 mostly done now
2016-04-18 changing usd holder
2016-04-18 moving things around
2016-04-18 some prodding
2016-04-19 cleaning up silk a little
2016-04-19 mostly routed
2016-04-20 6 airwires remain
2016-04-21 added pulldown to board
2016-04-21 added imu
2016-04-22 fixing outline
2016-04-24 zero airwires
2016-04-24 getting there now...
2016-04-24 half way thorugh checking
2016-04-24 DONE
2016-04-24 now actually done
2016-04-24 done attempt 3 (now with DRC)
2016-04-24 done attempt 4
2016-04-25 added final prototype 2 gerbers
2016-04-26 adding ST IMUs
2016-04-26 initial route with new imu
2016-04-26 changing some comments
2016-04-27 logo changeover
2016-04-28 Move outline to a part, including edge pads clean up outline around USB socket to make it easier to mill clean up major GND pours in board
2016-04-28 Simplify the micro python logo
2016-04-28 Clean up servo power pour
2016-04-28 Via's under wifi module
2016-04-29 Lots of clean up around via placement and trace angle swapped out micro python logo for silk only version
2016-04-29 Align fid's and last few tweaks
2016-04-29 Add Micro Python logo to front of PCB in white and gold version to compare with white only version on the back
2016-04-29 Move lanyard holes to board out line part
2016-04-29 moved switches down, changed imu wiring a little
2016-04-29 capacitor nudge
2016-04-29 Fix up via clearance
2016-04-29 minor silk change
2016-04-29 zipped gerbers for fab
2016-05-06 marking HSE crystal as DNP
2016-05-08 bom mostly complete (just order numbers for generic passives missing)
2016-05-13 Add full part for LCD out line. update LCD connector to connector part update some resistor parts name
2016-05-13 Give power switch a value
2016-05-17 mirroring LGA to correct them
2016-05-17 starting v0.3 boards, corrected LGA12,LGA14 pin assignments after mirroring
2016-05-17 Add CERN Open Hardware License
2016-05-17 updating usb resitors
2016-05-18 adding prototype 2 pinmap
2016-05-23 updated antenna footprint, screen cutout
2016-05-23 most parts moved to new position
2016-05-24 updating libraries
2016-05-24 Adding Alps SKPMAPE010 switch footprint
2016-05-24 v0.3 board outline updates and start of milling
2016-05-24 copying switch between libs
2016-05-24 cc spi clk moved to allow dac, led fet moved, ws2812 on timer
2016-05-24 sch mostly done for 0.3
2016-05-24 rearranged gpio, one gpio is now NC...
2016-05-24 all gpio now connected
2016-05-25 routing intensifies...
2016-05-25 getting there
2016-05-25 LBR: add combined switch
2016-05-25 8 airwires...
2016-05-25 LBR: screen mill cutout and drill for post
2016-05-25 switched switches
2016-05-25 LBR: mouse bites to PCB out line and milling
2016-05-25 LBR: small tweet to outline
2016-05-25 rerouting around screen
2016-05-25 lib -> sch, updating
2016-05-25 updating usd
2016-05-25 changing out diodes
2016-05-25 LBR: move top mouse bite over
2016-05-25 LBR: touch up WSON8 and HVSSOP10 foot print
2016-05-25 no overlap
2016-05-26 routing done
2016-05-26 some silk cleanup
2016-05-26 LBR: some silk clean up
2016-05-26 Angle and clearance tidy
2016-05-26 attempt to restore variant for eagle 6
2016-05-26 And again
2016-05-26 added testpoint for !HIB
2016-05-26 silk tidied
2016-05-26 minor corections
2016-05-26 fixing for eagle 6
2016-05-26 gpio relabel PB11->PB2
2016-05-26 Gerbers as sent to Ragworm for v0.3
2016-05-27 Rework entier power section layout on schematic
2016-06-01 changing 4R7 -> 12R, more schematic tidying
2016-06-02 Front silk and move joystick over 2mm
2016-06-02 LBR: LGA silk update
2016-06-03 π to a 1000 digits
2016-06-03 Starting final revision files
2016-06-03 Revert Prototype3 files to as sent for PCB fab
2016-06-03 LBR: correct MicroPython logo layering
2016-06-03 LBR: Adjust mouse bite holes
2016-06-03 Library updates
2016-06-03 LBR: Finish milling outline
2016-06-03 Pull in Board outline update
2016-06-03 Via to 0.3mm round
2016-06-03 Flip front text around
2016-06-04 LBR: Adding logos
2016-06-04 Sponsor logos to rear Note this moves the files to Eagle 7
2016-06-04 LBR: lots of updates, all parts added, symbols cleaned
2016-06-04 Lots of clean up in schematic
2016-06-05 More clean up
2016-06-05 LGA footprint clean up, still need to check tape pin1 in LGA12
2016-06-05 Last footprint change and lots a trace clean up done
2016-06-05 Last trace touch up's.
2016-06-06 Do Not use [t|b]Names layer for silkscreen It fuck things up when you panelize
2016-06-06 Final BRD commit do not change it again
2016-06-06 started gpio pinout fig
2016-06-06 Update all values for L4 variant by default
2016-06-07 cleaning up files
2016-06-07 updated board image and cleaned up
2016-06-15 LBR, Correct µSD Tape rotation
2016-06-20 Updating LED resistor values
2016-07-11 fixing error: line 7053, column 132: redefinition of name 'LOGO1' in tag <element>
2016-07-20 Production badge images
2016-07-20 Correct joystick trace names
2016-07-20 Correct joystick part in the LBR
2016-07-27 adding sandwich case
2016-07-27 apparently somethings chnaged
2016-07-28 updating pinouts
2016-07-28 adding pin name for neopix
2016-07-29 Add final schematic PDF on A3 and A0
2016-08-12 windows flash and upload done
2016-08-12 fixing for w7
2016-08-12 Publish Final Artwork files
2017-01-22 Added Loop Updater
